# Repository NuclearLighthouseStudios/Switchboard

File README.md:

# Switchboard

This repository contains the KiCAD project files for the Switchboard guitar pedal IO PCB,
designed to be used with my FX Box guitar pedal enclosure or as a handy interface board when breadboarding new effects.

It contains power filtering, input and output jacks, true bypass switching, a status LED and an optional LTC1044 voltage inverter to generate a -9V rail.  
Components numbered in the 10x rage are specific to the voltage inverter and can be left out if it's not needed.

If you just want the Gerber files or a PDF of the schematic check out the releases tab for downloads.

This PCB should be easily manufacturable with most online PCB houses by just uploading the gerber files.

The PCB and enclosure were designed to fit Neutrik NMJ4HCD2 jacks but most jacks that fit the footprint should be fine. Just make sure they have pins instead of lugs and use a ferrule for mounting instead of a nut.

The pin header should be a precision ground one since they're usually lower profile and taller headers might prevent the boards from fitting correctly.
Make sure yours are less than 7.5mm tall.

Check out the accompanying 3D printable enclosure here: https://github.com/NuclearLighthouseStudios/FXBox

## BOM

*All parts in the 10x range are optional and only for pedals that need a -9V supply.*

| Reference | Quantity | Value   | Description                                  |
| :-------- | -------: | ------: | :------------------------------------------- |
| C1 C103   | 2        | 100n    | Generic ceramic capacitor                    |
| C102      | 1        | 47µ     | Electrolytic capacitor, 16V                  |
| C101 C104 | 2        | 10µ     | Electrolytic capacitor, 16V                  |
| C2        | 1        | 100µ    | Electrolytic capacitor, 16V                  |
| D1        | 1        | LED     | 5mm LED                                      |
|           | 1        |         | 19mm LED standoff for D1                     |
| J4        | 1        |         | Pin Socket, 6 pins, 2.54mm spacing           |
| J3 J5     | 2        |         | Neutrik NMJ4HCD2 Jack                        |
| R1 R101   | 2        | 100     | Metal film resistor 1%, DIN 0207             |
| R2        | 1        | 10k     | Metal film resistor 1%, DIN 0207             |
| SW1       | 1        |         | 3PDT Footswitch                              |
| U101      | 1        | LTC1044 | LTC1044 Switched-Capacitor Voltage Converter |

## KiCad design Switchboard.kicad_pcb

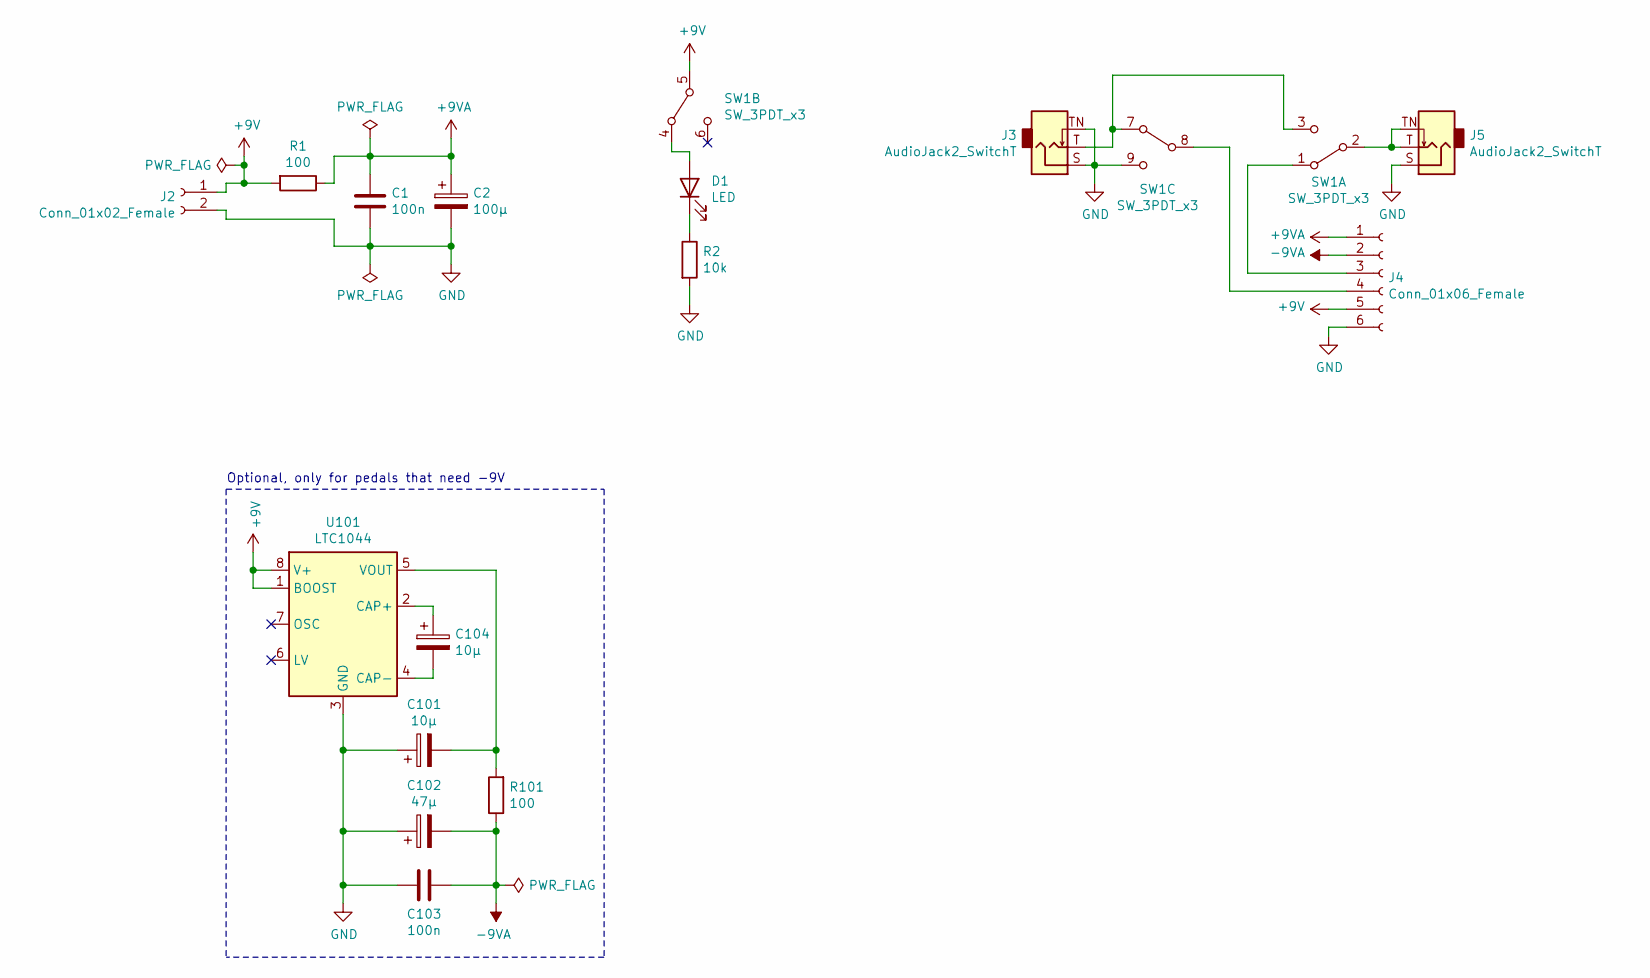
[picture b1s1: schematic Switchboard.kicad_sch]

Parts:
C1, C103: 100n; C_Disc_D3.0mm_W2.0mm_P2.50mm
C2: 100µ; CP_Radial_D6.3mm_P2.50mm
C101, C104: 10µ; CP_Radial_D5.0mm_P2.50mm
C102: 47µ; CP_Radial_D5.0mm_P2.50mm
D1: LED; LED_D5.0mm
J2: Conn_01x02_Female; SolderWire-0.5sqmm_1x02_P4.8mm_D0.9mm_OD2.3mm
J3, J5: AudioJack2_SwitchT; MonoJack_6.35mm_Neutrik_NMJ4HCD2
J4: Conn_01x06_Female; PinSocket_1x06_P2.54mm_Vertical
R1, R101: 100; R_Axial_DIN0207_L6.3mm_D2.5mm_P2.54mm_Vertical
R2: 10k; R_Axial_DIN0207_L6.3mm_D2.5mm_P7.62mm_Horizontal
SW1: SW_3PDT_x3; SW_3PDT_Footswitch
U101: LTC1044; DIP-8_W7.62mm

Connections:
+9V: J2.1, J4.5, R1.2, SW1.5 (B), U101.1 (BOOST), U101.8 (V+)
+9VA: C1.1, C2.1, J4.1, R1.1
-9VA: C102.2, C103.1, J4.2, R101.1
GND: C1.2, C2.2, C101.1, C102.1, C103.2, J2.2, J3.S, J3.TN, J4.6, J5.S, R2.2, SW1.9 (C), U101.3 (GND)
unnamed: C101.2, R101.2, U101.5 (VOUT)
unnamed: C104.1, U101.2 (CAP+)
unnamed: C104.2, U101.4 (CAP-)
unnamed: D1.1 (K), R2.1
unnamed: D1.2 (A), SW1.4 (A)
unnamed: J3.T, SW1.3 (C), SW1.7 (A)
unnamed: J4.3, SW1.1 (A)
unnamed: J4.4, SW1.8 (B)
unnamed: J5.T, J5.TN, SW1.2 (B)

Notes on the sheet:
Optional, only for pedals that need -9V

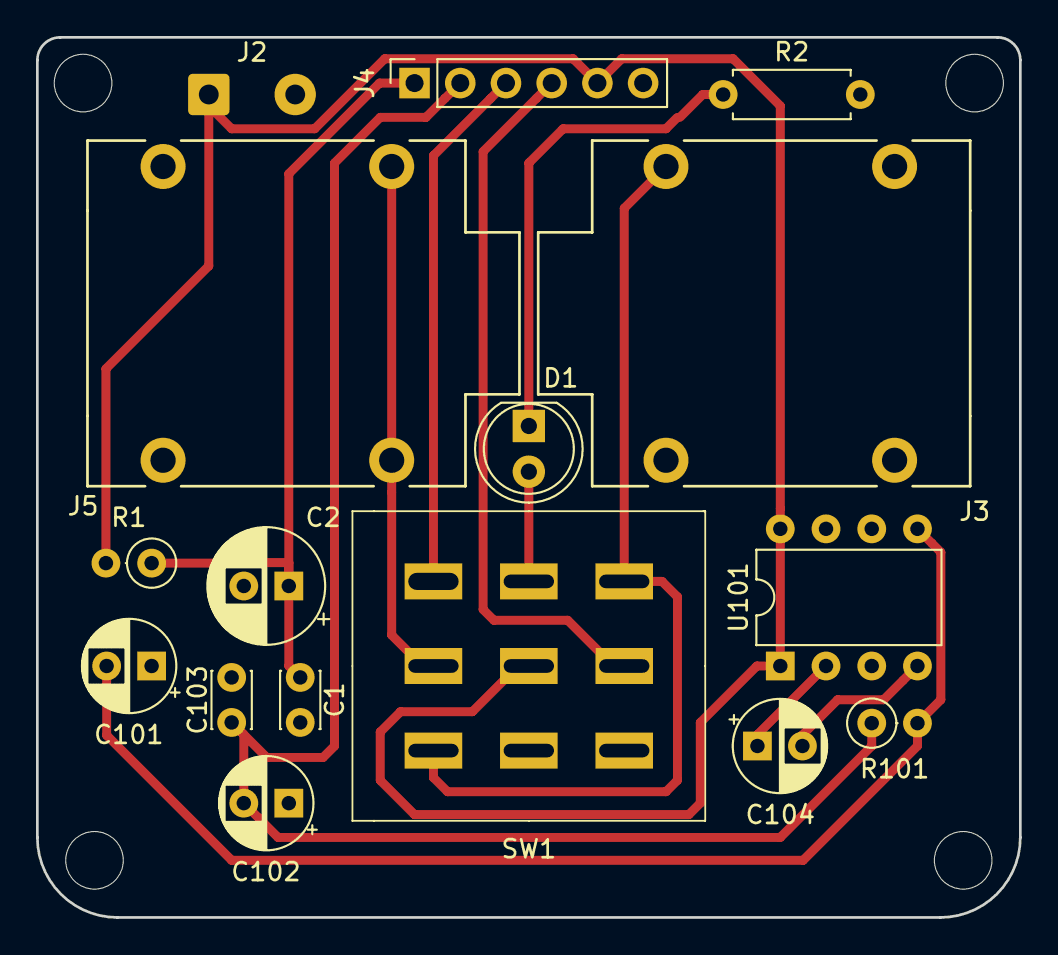
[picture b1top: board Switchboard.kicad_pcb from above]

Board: 2 copper layers, 54.6 x 48.9 mm, 16 parts (0 on the bottom side), 13 nets.

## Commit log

2020-02-23 Initial Commit! Whoo!
2020-02-23 Update Zone Fills
2020-03-10 Add readme
2020-12-30 Tweak some resistor values
2020-12-30 Update README with BOM
2021-03-25 Add LED standoff to BOM and add note about optional parts
2022-08-14 Migrate to KiCAD 6!
2022-08-14 Update symbols and footprints
2022-08-14 Fix DRC errors
2022-08-16 Update link to enclosure

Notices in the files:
Switchboard.kicad_pcb:
CC BY-NC-SA
